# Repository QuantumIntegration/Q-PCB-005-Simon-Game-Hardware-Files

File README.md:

# Quantum DIY Kit Hardware Files - Simon Game
## Introduction

This repository contains all the hardware files necessary to build the PCBs and assemble the DIY kits. The PCBs can be ordered from for example [JLCPCB](https://jlcpcb.com/) or [PCBWay](https://www.pcbway.com/). The components can be sourced mostly from [Amazon](https://amazon.com/) or [Digikey](https://digikey.com/), according to the links in the BOM file.

## Download the correct revision

If you are nor familiar with the git version control system, please follow these simple steps to download your version of the DIY kit

<em>1. Click the branch button</em>

<em>2. Select the branch matching your revision</em>

<em>3. Click the Code button</em>

<em>4. Download the ZIP and extract it on your machine</em>

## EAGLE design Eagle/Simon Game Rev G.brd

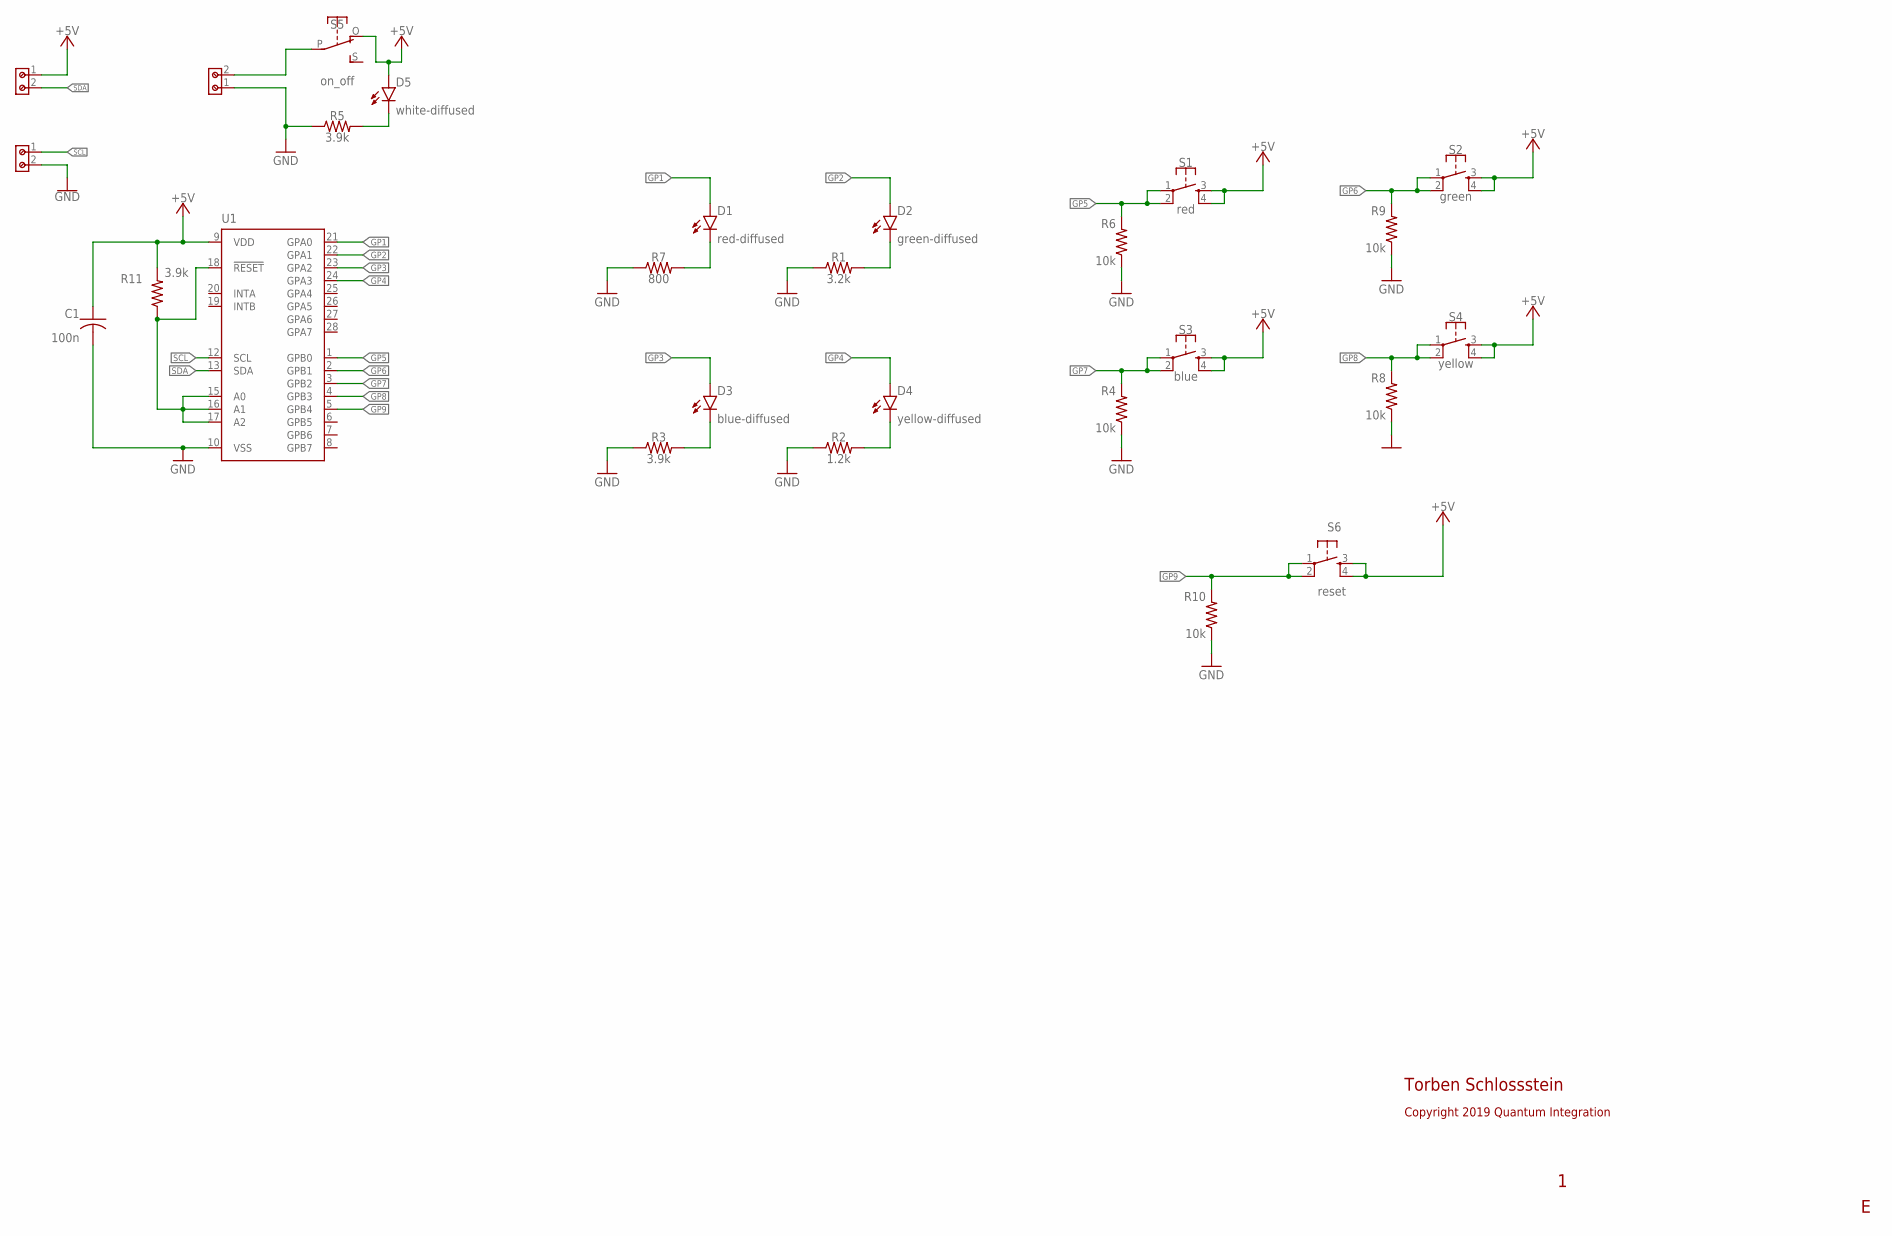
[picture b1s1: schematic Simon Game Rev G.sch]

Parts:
C1: 100n; C050-024X044
D1: red-diffused; LED5MM
D2: green-diffused; LED5MM
D3: blue-diffused; LED5MM
D4: yellow-diffused; LED5MM
D5: white-diffused; LED5MM
J1, J2, J3: 691214110002
R1: 3.2k; 0207/10
R2: 1.2k; 0207/10
R3, R5, R11: 3.9k; 0207/10
R4, R6, R8, R9, R10: 10k; 0207/10
R7: 800; 0207/10
S1: red; B3F-40XX
S2: green; B3F-40XX
S3: blue; B3F-40XX
S4: yellow; B3F-40XX
S5: on_off; EG1270-90
S6: reset; B3F-10XX
U1: MCP23017; DIL28-3

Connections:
+5V: C1.1, D5.A, J2.1, R11.2, S1.3 (S), S1.4 (S1), S2.3 (S), S2.4 (S1), S3.3 (S), S3.4 (S1), S4.3 (S), S4.4 (S1), S5.O, S6.3 (S), S6.4 (S1), U1.9 (VDD)
GND: C1.2, J1.1, J3.2, R1.1, R2.1, R3.1, R4.1, R5.1, R6.1, R7.1, R8.1, R9.1, R10.1, U1.10 (VSS)
GP1: D1.A, U1.21 (GPA0)
GP2: D2.A, U1.22 (GPA1)
GP3: D3.A, U1.23 (GPA2)
GP4: D4.A, U1.24 (GPA3)
GP5: R6.2, S1.1, S1.2 (P1), U1.1 (GPB0)
GP6: R9.2, S2.1, S2.2 (P1), U1.2 (GPB1)
GP7: R4.2, S3.1, S3.2 (P1), U1.3 (GPB2)
GP8: R8.2, S4.1, S4.2 (P1), U1.4 (GPB3)
GP9: R10.2, S6.1, S6.2 (P1), U1.5 (GPB4)
unnamed: D1.K (C), R7.2
unnamed: D2.K (C), R1.2
unnamed: D3.K (C), R3.2
unnamed: D4.K (C), R2.2
unnamed: R11.1, U1.15 (A0), U1.16 (A1), U1.17 (A2), U1.18 (!RESET)
unnamed: J1.2, S5.P
unnamed: D5.K (C), R5.2
SCL: J3.1, U1.12 (SCL)
SDA: J2.2, U1.13 (SDA)

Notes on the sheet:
Copyright 2019 Quantum Integration
Torben Schlossstein

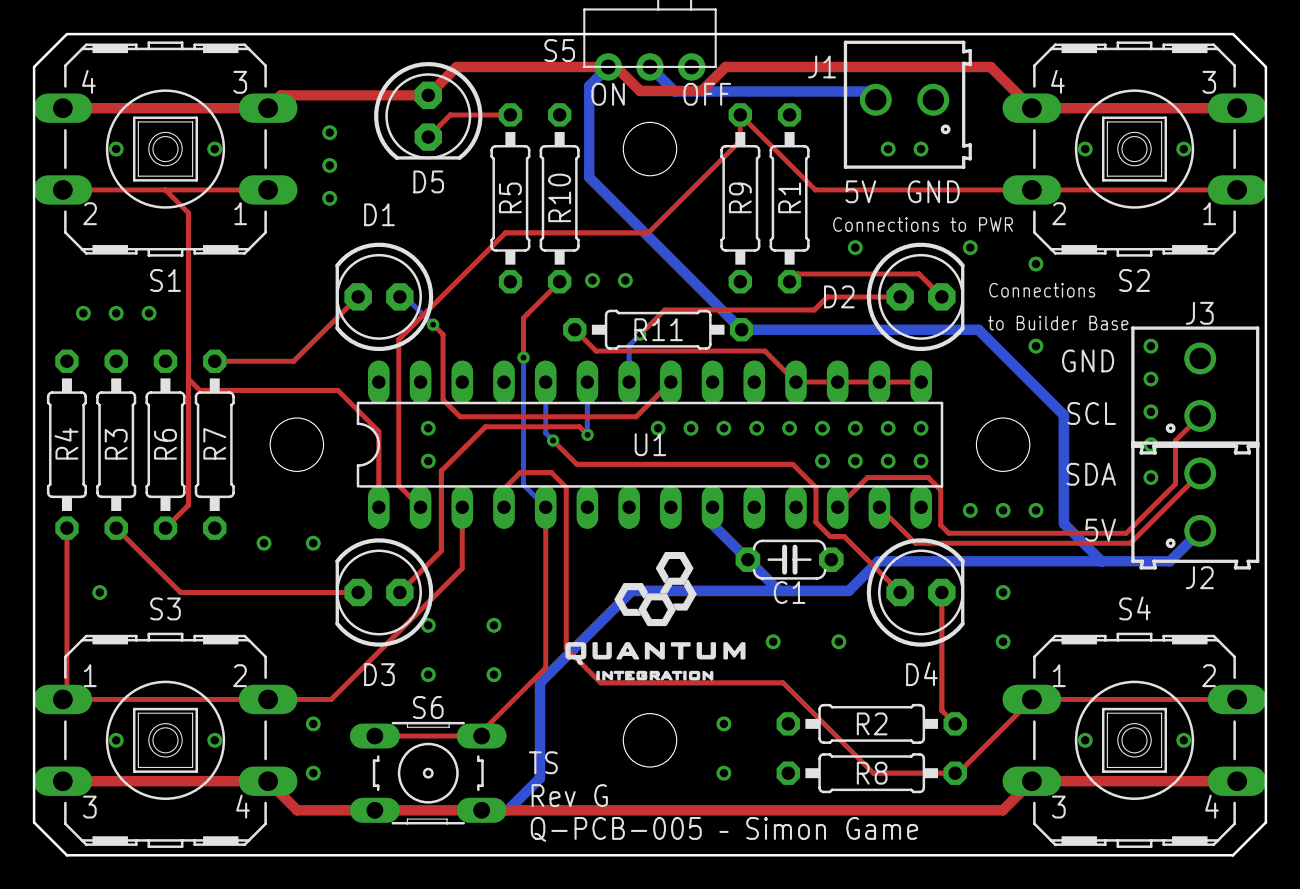
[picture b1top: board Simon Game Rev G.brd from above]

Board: 2 copper layers, 75.0 x 50.0 mm, 27 parts (0 on the bottom side), 20 nets.

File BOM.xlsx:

Index | Part | Value | Quantity | Designators | Package | Comments | Specific Part Reference | Part Link Example
1 | Terminal |  | 3 | J1, J2, J3 |  | 3.50mm, 1x2 |  | https://www.digikey.com/product-detail/en/w%C3%BCrth-elektro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
2 | MCP23017 |  | 1 | U1 | DIP-28 |  |  | https://www.digikey.com/en/products/detail/microchip-technol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
3 | Slide Switch |  | 1 | S5 |  | 90 degree | EG1270 | https://www.digikey.com/product-detail/en/e-switch/EG1270/EG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
4 | Ceramic Capacitor | 100n | 1 | C3 | 024x044 |  |  | https://www.digikey.com/product-detail/en/kemet/C315C104M5U5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
5 | Resistor | 1.2k | 1 | R2 | 0207/10 | 1/4 W |  | https://www.amazon.com/SIQUK-Resistors-Resistor-Assortment-E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
6 | Resistor | 10k | 5 | R4, R6, R8, R9, R10 | 0207/10 | 1/4 W |  | https://www.amazon.com/SIQUK-Resistors-Resistor-Assortment-E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
7 | Resistor | 3.2k | 1 | R1 | 0207/10 | 1/4 W |  | https://www.amazon.com/SIQUK-Resistors-Resistor-Assortment-E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
8 | Resistor | 3.9k | 3 | R3, R5, R11 | 0207/10 | 1/4 W |  | https://www.amazon.com/SIQUK-Resistors-Resistor-Assortment-E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
9 | Resistor | 800 | 1 | R7 | 0207/10 | 1/4 W |  | https://www.amazon.com/SIQUK-Resistors-Resistor-Assortment-E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
10 | Tactile Button |  | 1 | S6 | B3F-10xx |  | Omron B3F-1020 | https://www.digikey.com/en/products/detail/omron-electronics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
11 | LED | green-diffused | 1 | D2 | 5mm |  |  | https://www.amazon.com/Diffused-Lighting-Electronics-Compone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
12 | LED | red-diffused | 1 | D1 | 5mm |  |  | https://www.amazon.com/Diffused-Lighting-Electronics-Compone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
13 | LED | blue-diffused | 1 | D3 | 5mm |  |  | https://www.amazon.com/Diffused-Lighting-Electronics-Compone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
14 | LED | yellow-diffused | 1 | D4 | 5mm |  |  | https://www.amazon.com/Diffused-Lighting-Electronics-Compone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
15 | LED | white-diffused | 1 | D5 | 5mm |  |  | https://www.amazon.com/Diffused-Lighting-Electronics-Compone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
16 | Tactile Button |  | 1 | S3 | B3F-40xx | blue round color cap | Omron B3F-4055, Blue round Cap | https://www.digikey.com/product-detail/en/omron-electronics-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
17 | Tactile Button |  | 1 | S1 | B3F-40xx | red round color cap | Omron B3F-4055, Red round Cap | https://www.digikey.com/product-detail/en/omron-electronics-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
18 | Tactile Button |  | 1 | S2 | B3F-40xx | green round color cap | Omron B3F-4055, Green round Cap | https://www.digikey.com/product-detail/en/omron-electronics-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
19 | Tactile Button |  | 1 | S4 | B3F-40xx | yellow round color cap | Omron B3F-4055, Yellow round Cap | https://www.digikey.com/product-detail/en/omron-electronics-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
20 | 28 pin carrier |  | 1

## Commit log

2021-03-16 edited readme and gitignore
2021-03-16 added project content
2021-03-16 edited readme title
2021-03-16 added readme preview
2021-04-22 corrected cap designator in BOM
2021-05-11 updated BOM resistor values
2021-05-15 added Arduino files and instructions
2021-08-17 added schematic as PDF

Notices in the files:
parts and their libraries:
Wurth_Connectors_WR-TBL Rising Cage Clam: Copyright: Würth Elektronik
